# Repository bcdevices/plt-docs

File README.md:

# plt-docs

Reference material for BCD's
[Production Line Tool (PLT)](https://www.bcdevices.com/plt/)

- [GetPLT](https://plt.bcdevices.com/): PLT Support Site
- [PLT Announcements](https://plt.bcdevices.com/hc/en-us/sections/360002542332-Announcements)
- [Blue Clover Devices](https://www.bcdevices.com/)

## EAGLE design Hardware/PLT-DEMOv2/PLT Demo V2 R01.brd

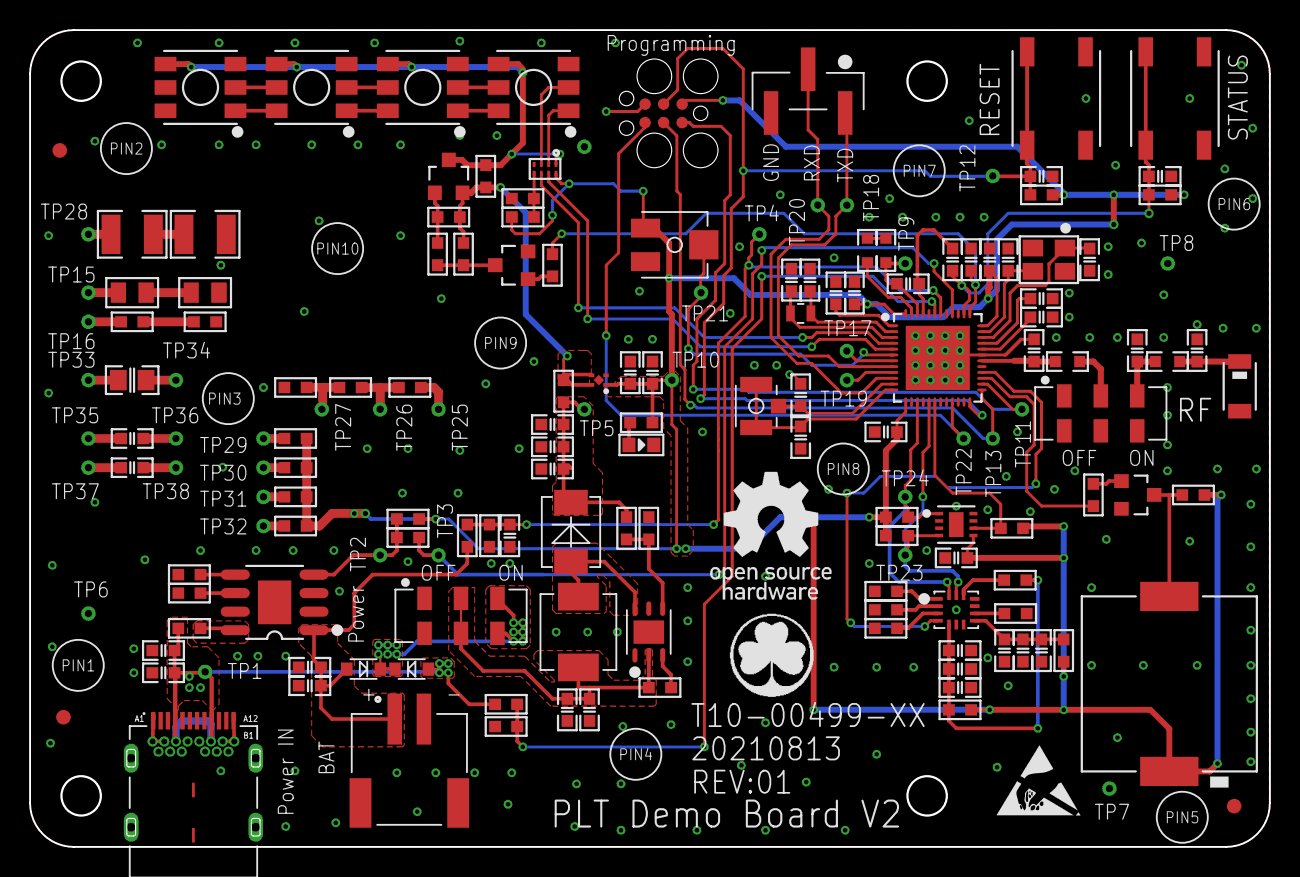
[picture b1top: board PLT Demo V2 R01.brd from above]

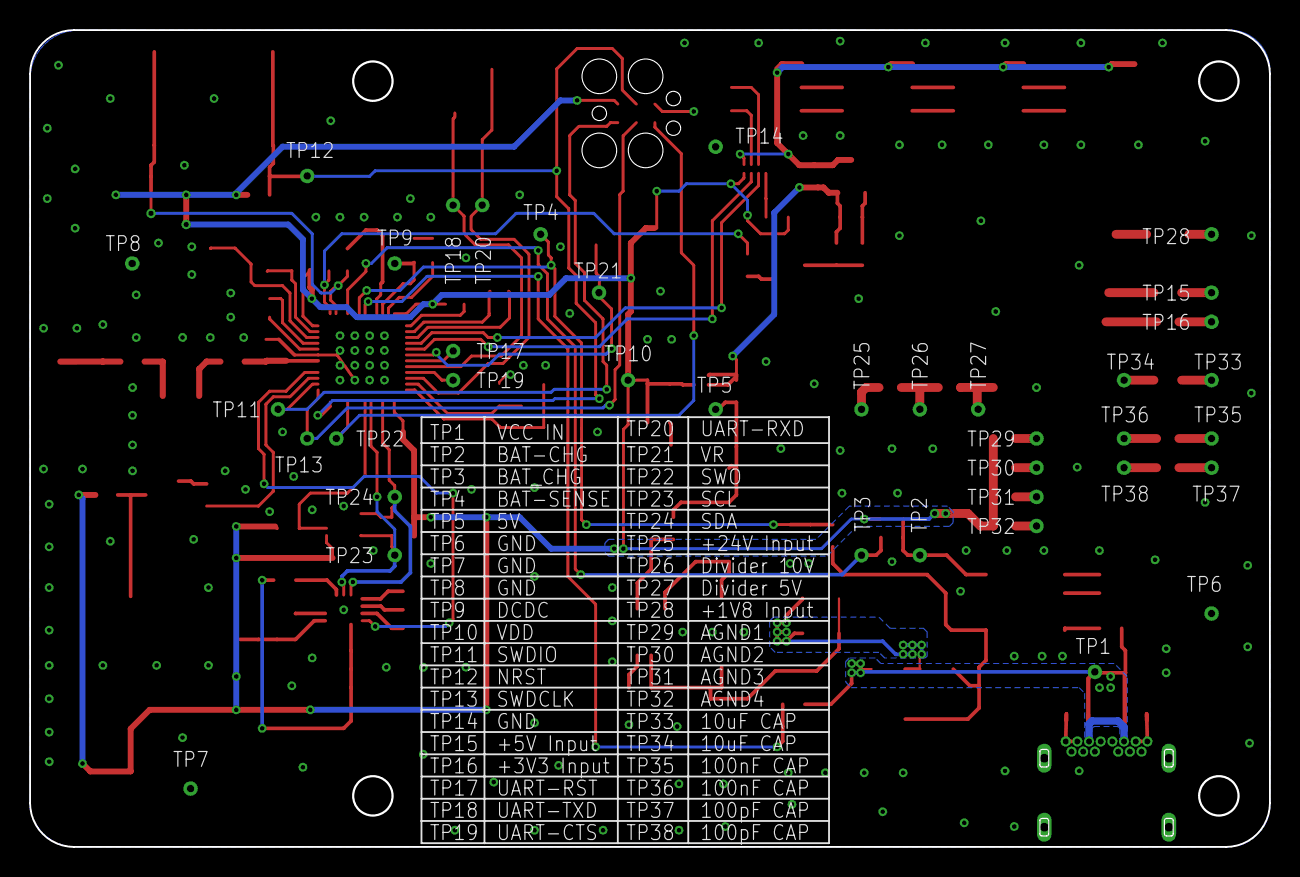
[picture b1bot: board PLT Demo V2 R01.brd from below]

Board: 2 copper layers, 85.0 x 56.0 mm, 181 parts (38 on the bottom side), 94 nets.

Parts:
ANT1: AMCA31-2R450G-S1F-T3; ANT_3216
C1, C3, C12: 10uF; C0603
C2, C4, C11, C13, C15, C18, C20, C27, C28, C32, C37, C43: 100nF; C0603
C5: 22nF; C0603
C6, C16, C19, C21, C23, C33: 12pF; C0603
C7, C8, C9, C10: 22uF; C0603
C14: 1uF; C0603
C17: 4.7uF; C0603
C22, C44: 100pF; C0603
C24, C26, C34: NC; C0603
C25: 0.8pF; C0603
C29, C30: 68pF; C0603
C31, C38: 2.2uF; C0603
C35, C36: 10nF; C0603
C39: 0.1uF; C0603
C42: 10uF; C0805
D1: B340LB-13-F; SMB
D4, D5, D6, D7: APA102C; LED5X5-6N
D8: Green; LED0603
D9, D10: CUS10S30,H3F; SOD-323
FID1, FID2, FID3: SENSOR_MISC_FIDUCIAL-1MM
J1: 632723300011; 632723X00011
J2: S2B-PH-SM4-TB(LF)(SN)
J3: U.FL-R-SMT(10)
JP1: TSM-103-01-F-SV-P-TR; JMP254P1X3V-SMT
L1: IHLP2020BZER5R6M01; IND-5220_SMD
L3: 15nH; IND-0603
L4: 10uH; IND-0603
L5: 3.9nH; IND-0603
L6: 12pF; IND-0603
P1: TC2030-MCP-NL; TC2030-IDC
PIN1, PIN2, PIN3, PIN4, PIN5, PIN6, PIN7, PIN8, PIN9, PIN10: PRESS-PINS
Q1, Q2: MMBT3904-TP; SOT23
Q3: FDN340P; SOT23
R1: 10M; R0603
R2: 2.2M; R0603
R3, R9, R12, R24, R33, R49, R50: 10K; R0603
R4, R7: 470R; R0603
R5, R34, R35, R57, R58, R59, R60: 4.7K; R0603
R6, R13, R15, R16, R18, R21, R25, R43: 0R; R0603
R8: 30K; R0603
R10, R30: 100K; R0603
R11, R14, R17, R23, R28: 47K; R0603
R20, R32, R46, R47: NC; R0603
R22: 43K; R0603
R29, R31: 470K; R0603
R48: 28K; R0603
R51, R54: 0.82R; R1210
R52, R55: 15R; R0805
R53, R56: 243K; R0603
SP1: PKLCS1212E4001R1; SPEAKER12X12_SMT
SW1, SW2: EVQ-Q2F01W; SWITCH6.5X6_SMD
SW3, SW4: JS202011JCQN
TP1, TP2, TP3, TP4, TP5, TP6, TP7, TP8, TP9, TP10, TP11, TP12, TP13, TP14, TP15, TP16, TP17, TP18, TP19, TP20, TP21, TP22, TP23, TP24, TP25, TP26, TP27, TP28, TP29, TP30, TP31, TP32, TP33, TP34, TP35, TP36, TP37, TP38: TPTP1.0X0.5_DIP; TP1.0X0.5_DIP
U1: XC6804A3E1QR-G; SOP127P6X1.6-8NP
U2: LMR62421XSDE/NOPB; WSON095P3X3-6NPAD
U3: NCP161BMX330TBG; XDFN4
U4: SHT30-DIS; DFN050P2.5X2.5-8N
U5: NRF52832-QFAA-R; QFN040P6X6-48NV
U6: BMI160; LGA050P3X2.5-14N
U7: 74LVCH2T45GT,115; XSON8-SOT833-1
U$4: BCD-LOGO
U$5: ANTI-STATIC
U$6: OSHW-LOGO-R2000
VR1: 3314J-1-103E
Y1: 7V-32.000MDDE-T; OSC3.2X2.5-4N
Y2: 9HT11-32.768KDZF-T; OSC2X1.2-2N

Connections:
5V: Q3.2, R6.1, R29.2, R31.1, R32.2, U3.3, U3.4
5V_LED: D4.4, D5.4, D6.4, D7.4, Q3.3, R32.1, U7.1
+1V8OUT: R51.2, TP28.1
+3V3OUT: R53.2, TP16.1
+5VOUT: R52.2, TP15.1
+24V: R48.2, TP25.1
AGND1: R57.1, TP29.1
AGND2: R58.1, TP30.1
AGND3: R59.1, TP31.1
AGND4: R60.1, TP32.1
BAT: C3.1, C4.1, D9.1, J2.1, R1.2, U1.1
BAT_CHGB: R25.1, TP3.1, U5.40
BAT_CHGB2: R24.1, R25.2, TP2.1, U1.4
BAT_SENSE: C5.1, R1.1, R2.2, TP4.1, U5.42
BUTTON1: C6.1, C15.1, R11.1, SW1.1, SW1.2, U5.38
BUZZER: R5.1, U5.27
DCDC: C14.1, L3.1, TP9.1, U5.46
GND: C1.2, C2.2, C3.2, C4.2, C5.2, C6.2, C7.2, C8.2, C9.2, C10.2, C11.2, C12.2, C13.2, C14.2, C15.2, C16.2, C17.2, C18.1, C19.2, C20.2, C21.1, C22.2, C23.1, C24.2, C25.2, C26.2, C27.2, C28.2, C29.2, C30.2, C31.2, C32.2, C33.2, C34.2, C35.2, C36.2, C37.2, C38.2, C39.1, D4.3, D5.3, D6.3, D7.3, D8.2, J1.A1, J1.A12, J1.B1, J1.B12, J1.GND, J1.GND1, J1.S1, J1.S2, J1.S3, J1.S4, J1.S5, J1.S6, J2.2, J2.S1, J2.S2, JP1.3, P1.5, Q1.2, Q2.2, R2.1, R3.1, R9.1, R12.1, R13.2, R17.1, R21.1, R23.1, R46.2, R47.2, R50.1, R54.1, R55.1, R56.1, SW1.3, SW1.4, SW2.3, SW2.4, TP6.1, TP7.1, TP8.1, TP14.1, U1.3, U1.9, U2.1, U2.5, U2.7, U3.2, U3.5, U4.2, U4.7, U4.8, U4.9, U5.31, U5.45, U5.49, U5.P$1, U5.P$2, U5.P$3, U5.P$4, U5.P$5, U5.P$6, U5.P$7, U5.P$8, U5.P$9, U5.P$10, U5.P$11, U5.P$12, U5.P$13, U5.P$14, U5.P$15, U5.P$16, U6.6, U6.7, U7.4, VR1.1, Y1.2, Y1.4
I2C_SCL: R35.1, TP23.1, U4.4, U5.17, U6.13
I2C_SDA: R34.1, TP24.1, U4.1, U5.15, U6.14
INT1: U5.28, U6.4
unnamed: R47.1, U6.3
unnamed: D1.1, L1.2, U2.6
unnamed: C7.1, C8.1, L1.1, R10.2, SW4.2, SW4.5, U2.2
unnamed: R10.1, U2.3
unnamed: R3.2, U1.5
unnamed: R43.1, U1.8
unnamed: R8.1, R9.2, U2.4
unnamed: C9.1, C10.1, C11.1, D1.2, R6.2, R8.2, TP5.1
unnamed: C18.2, U5.1
unnamed: C21.2, U5.2, Y2.1
unnamed: D8.1, R7.1
unnamed: R12.2, U1.6
unnamed: Q2.3, R29.1, R30.2
unnamed: Q2.1, R28.1
unnamed: Q3.1, R30.1, R31.2
unnamed: C23.2, U5.3, Y2.2
unnamed: C30.1, J3.2, J3.3, U5.12
unnamed: C29.1, J3.1, U5.11
unnamed: R13.1, U6.1
unnamed: C25.1, L5.1, U5.30
unnamed: L3.2, L4.1
unnamed: L4.2, U5.47
unnamed: D4.1, U7.2
unnamed: D4.2, U7.3
unnamed: D4.6, D5.1
unnamed: D4.5, D5.2
unnamed: D5.6, D6.1
unnamed: D5.5, D6.2
unnamed: D6.6, D7.1
unnamed: D6.5, D7.2
unnamed: R17.2, U6.9
unnamed: R20.1, R21.2, U7.5
unnamed: C16.1, U5.35, Y1.3
unnamed: Q1.3, R4.1, SP1.2
unnamed: Q1.1, R5.2
unnamed: C19.1, U5.34, Y1.1
unnamed: C22.1, U5.33
unnamed: C24.1, U5.32
unnamed: L5.2, SW3.2
unnamed: C26.1, L6.1, SW3.3
unnamed: ANT1.1, C34.1, L6.2
unnamed: C31.1, C32.1, C35.1, R15.1, R16.1, U6.5
unnamed: R16.2, U6.12
unnamed: C36.1, C37.1, C38.1, R18.1, U6.8
unnamed: R51.1, R54.2
unnamed: R52.1, R55.2
unnamed: R53.1, R56.2
unnamed: R46.1, U6.2
unnamed: D9.2, D10.2, SW4.3, SW4.6
unnamed: R49.1, R50.2, TP27.1
unnamed: R48.1, R49.2, TP26.1
unnamed: C42.2, TP34.1
unnamed: C42.1, TP33.1
unnamed: C43.2, TP36.1
unnamed: C43.1, TP35.1
unnamed: C44.2, TP38.1
unnamed: C44.1, TP37.1
NRST: C28.1, P1.3, R14.2, SW2.1, SW2.2, TP12.1, U5.24
PWR_EN: C33.1, R28.2, U5.37
RGBLED_MOSI: U5.5, U7.7
RGBLED_SCK: U5.4, U7.6
SHT30_RESET: R33.1, U4.6, U5.18
SWDCLK: P1.4, TP13.1, U5.25
SWDIO: P1.2, TP11.1, U5.26
SWO: P1.6, TP22.1, U5.21
UART_CTS: TP19.1, U5.9
UART_RTS: TP17.1, U5.7
UART_RXD: JP1.2, TP20.1, U5.10
UART_TXD: JP1.1, TP18.1, U5.8
USB_DETECT: R22.1, R23.2, U5.43
VBUS: C1.1, C2.1, D10.1, J1.A4, J1.A9, J1.B4, J1.B9, R22.2, R43.2, TP1.1
VDD: C12.1, C13.1, C17.1, C20.1, C27.1, C39.2, P1.1, R4.2, R7.2, R11.2, R14.1, R15.2, R18.2, R20.2, R24.2, R33.2, R34.2, R35.2, R57.2, R58.2, R59.2, R60.2, SP1.1, TP10.1, U3.1, U4.5, U5.13, U5.36, U5.48, U7.8, VR1.3
VR: TP21.1, U5.6, VR1.2

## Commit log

2018-12-04 suite-demo1-BLE: nRF52DK test plan
2018-12-31 Add STM32L4DK-IOT example
2019-01-04 Add suite-scan.yaml
2019-01-11 Add ly10 demo FW v0.1.0
2019-01-11 Add ly10 demo FW v0.1.0 (#1)
2019-01-17 Add LY10-DEMO firmware v0.1.4, v0.1.5, v0.1.6
2019-01-17 Add LY10-DEMO firmware v0.1.4, v0.1.5, v0.1.6 (#2)
2019-01-17 Update README.md (#3)
2019-01-21 LY10-DEMO: v0.1.7, v0.1.8
2019-01-21 LY10-DEMO: v0.1.7, v0.1.8 (#4)
2019-03-08 Add Test Suite Reference v0.4.7
2019-03-08 Add Test Suite Reference v0.4.7 (#5)
2019-03-09 Update to Test Plan Reference v0.4.8 (#6)
2019-03-09 rename
2019-03-28 Update TestPlanReference to v0.4.9 (#7)
2019-03-31 Update TestPlanReference to v0.5.0
    - Document `freq` command
    - Document `measure` command
    - Document `mux` command
    - Document `pin` command
    - Document `power` command
    - Document `short` command
2019-03-31 Update TestPlanReference to v0.5.0 (#8)
    - Document `freq` command
    - Document `measure` command
    - Document `mux` command
    - Document `pin` command
    - Document `power` command
    - Document `short` command
2019-04-09 Document ESP32 DevKitC hookup
2019-04-09 README: update link
2019-04-09 Document ESP32 DevKitC hookup (#9)
    * Document ESP32 DevKitC hookup
    * README: update link
2019-04-10 PLT-200A: rear DUT connectors
2019-04-10 PLT-200A: rear DUT connectors (#10)
2019-04-10 PLT-200A probes and signals
2019-04-10 PLT-200A probes and signals (#11)
2019-04-11 Add PLT-200A test probe assignments Excel template
2019-04-15 Document programming CC1352
2019-04-15 Document programming CC1352 (#12)
2019-04-16 Add TestPlanReference v0.5.1
2019-04-18 LY10-DEMO: update for PLT-200A
2019-04-19 Add drawings for PLT-200A rear IDC receptacles
2019-05-13 Add LY10-DEMO ICT test plan v1.2
2019-05-14 Add TestPlanReference v0.5.2
2019-05-14 Add NFC write example
2019-07-02 update README (#13)
2019-07-02 Add PLT-200A Specificaition Sheet v0.5.1
2019-07-02 Add PLT-200A Specificaition Sheet v0.5.1 (#15)
2019-07-18 nRF52DK: Add example firmware
2019-07-18 nRF52DK: Add HRS firmware (#16)
    * nRF52DK: Add example firmware
2019-07-22 ICTDemoTestPlanV1.3.yaml
    Update of ICTDemoTestPlanV1.2.yaml, where the impedance range for ICT-005 was changed to >-1Ohm.
2019-07-24 Add Zephyr-based LY10 demo firmware
2019-07-24 Add Zephyr-based LY10 demo firmware (#18)
2019-07-24 Rename
    * Rename
2019-08-15 ICTZephyrTestPlanV1.3: Fix firmware HEX path
2019-08-15 ICTZephyrTestPlanV1.3: Fix firmware HEX path (#20)
2019-08-15 suite-stm32l4DK-IOT-BLE.yaml: Fix firmware path
2019-08-15 suite-stm32l4DK-IOT-BLE.yaml: Fix firmware path (#21)
2019-08-19 Add ATMega168PB example project
2019-08-19 Add ATMega168PB example project (#22)
2019-08-19 Add manual v0.5.6
2019-08-19 Dev/manual 0.5.6 (#23)
    * Add ATMega168PB example project
    * Add manual v0.5.6
2019-08-21 CC1352 Project: Update README
2019-08-21 STM32L4DK-IOT: Update README
2019-08-21 nRF52DK Project: Update README
2019-08-21 Atmel AVR ATmega168P/PB Project: update README
2019-08-21 README.md: update
2019-08-21 README.md: update (#25)
2019-08-21 Add nRF91 DK Project
2019-08-21 update README links
2019-08-21 nRF91 DK: Program via SWD
2019-08-21 Add nRF91 DK Project (#26)
    * Add nRF91 DK Project
    * update README links
    * nRF91 DK: Program via SWD
2019-08-22 Test Plan Reference v0.5.7
2019-08-26 PLT-200A Specification Sheet v0.5.8
2019-08-26 PLT-200A Specification Sheet v0.5.8 (#28)
2019-09-19 System Manual v0.6.0
2019-09-19 System Manual v0.6.0 (#29)
2019-09-19 System Manual v0.6.1
2019-09-19 System Manual v0.6.1 (#30)
2019-09-19 Remove older docs
2019-09-19 Remove older docs (#31)
2019-10-04 PLT System Documentation v0.6.2
2019-10-04 Add links to latest PDFs
2019-10-08 PLT System Documentation v0.6.3
2019-10-08 PLT System Documentation v0.6.3 (#32)
2019-10-08 PLTcloud spec sheet
2019-10-08 PLTcloud spec sheet (#33)
2019-11-05 ICT spec sheet
2019-11-05 ICT spec sheet (#34)
2019-11-07 Add TestPlanReference-0.6.5.pdf
2019-12-30 Duplicate Test probe assignments TEMPLATE under new name
2020-02-20 v0.6.7 spec sheets
2020-02-20 STM32L4DK-IOT: Use STM32L4_IoT_STLink target name
2020-02-20 suite-hrs-BLE: Use nRF52_JLink target name
2020-02-20 at_client-JLink: Use nRF91_JLink target name
2020-02-20 Add STM32F4DISCOVERY example project
2020-02-20 Add STM32F4DISCOVERY example project (#35)
2020-02-21 Test Plans for AT-based GSM modems
2020-02-21 Test Plans for AT-based GSM modems (#36)
2020-02-22 Test Plans for Nucleo F401RE board
2020-02-22 Test Plans for Nucleo F401RE board (#37)
2020-02-22 Test Plans for Nucleo L432KC board
2020-02-24 Zephyr sample for STM32Nucleo-F207ZG
2020-02-24 Zephyr sample for nRF52DK
2020-02-24 Zephyr sample for nRF91DK
2020-02-24 Zephyr sample for nRF52DK (#39)
2020-02-24 Zephyr sample for nRF91DK (#40)
2020-02-24 Update HEX files
2020-02-24 Zephyr sample for STM32Nucleo-F207ZG (#38)
    * Zephyr sample for STM32Nucleo-F207ZG
2020-02-24 Add TestPlanReference 0.6.8
2020-02-24 Zephyr sample for NXP LPCXpresso 11C24
2020-02-24 Add zephyr nRF91 example project (#41)
    * Zephyr sample for nRF91DK
    * Add TestPlanReference 0.6.8
2020-02-24 Zephyr sample for NXP LPCXpresso 11C24 (#42)
2020-02-24 README.md: Fix title
2020-02-24 STM32F4 Discovery Zephyr CAN sample
2020-02-24 STM32F4 Discovery Zephyr CAN sample (#43)
2020-02-26 README.md: Add LPCXpresso 11C24, Nucleo F207ZG
2020-03-06 Add PNEV7462C example Project
2020-03-06 Add PNEV7462C example Project (#44)
2020-03-09 TPM: Add GND
2020-03-09 TPM: Add GND (#45)
    Update test point matrix to include GND
2020-03-09 Examples: remove 'none' from program commands
2020-03-09 Examples: remove 'none' from program commands (#46)
2020-03-31 Add PSoC6 example
2020-04-22 LPCXpresso11C24: Add CMSIS-DAP example
2020-05-01 Add PSoC4 example
2020-07-17 Add EFM32-STK3800 example
2020-08-13 Add Microchip Explorer 8 / PIC18F25K20 example
2020-12-22 Add ATSAME54-XPro Zephyr sample project
2021-04-27 Move targets
2021-04-27 Targets to Boards
2021-04-27 PLT-DEMO
2021-04-28 PLT-DEMO: Rename artefacts to PLT-DEMO-..
2021-04-28 Projects: update README
2021-08-23 ATSAME54-XPro: README
2021-08-23 ATSAME54-XPro: README images
2021-08-23 ATSAME54-XPro: README cable pitch
2021-08-31 ATSAME54-XPro: 5 second delay after erase
2021-09-28 Add PLT-DEMOv2 schematics
2021-09-28 move
2021-09-28 Add CERN Open Hardware Licence Version 2 - Strongly Reciprocal
2021-12-17 Add Zephyr blinky example for TI CC1352r1_launchxl, update example test plan.
2021-12-20 Add ESP32 Zephyr hello_world sample.
2021-12-21 Add ESP32 Zephyr hello_world sample. (#48)
2022-10-28 Add nucleo-h753 examples.
2022-10-28 Fix directory name.
2022-10-28 Fix file names.
2022-10-31 Add example projects for NUCLEO-F070RB and NUCLEO-L152RE.
2022-11-02 Adjust STM32L1 programming target to STM32L1_Cat456.
    There are 6 categories of STM32L1, with different memory structures.
2022-11-02 Add example projects for NUCLEO-F070RB and NUCLEO-L152RE. (#50)
    * Add example projects for NUCLEO-F070RB and NUCLEO-L152RE.
    * Adjust STM32L1 programming target to STM32L1_Cat456.
    There are 6 categories of STM32L1, with different memory structures.
2022-11-02 Add example project for NUCLEO-H753ZI (#49)
    * Add nucleo-h753 examples.
    * Fix directory name.
    * Fix file names.
2022-11-07 Add example project for Raspberry Pi Pico, using USB Mass Storage
2022-11-09 Add example project for Raspberry Pi Pico, using USB Mass Storage (#51)
2023-01-26 Add example project for Analog Devices MAX32690EVKit
2023-01-26 Add example project for Analog Devices MAX32690EVKit (#52)
2023-02-16 Add example project for ST NUCLEO-G474RE.
2023-02-20 Add example project for ST NUCLEO-G474RE. (#53)
2023-03-20 cleanups
2023-03-20 link fixes
2023-03-20 cleanup
2023-03-20 Update pltdemov2 README.md (#54)
2023-03-29 yamllint
2023-03-29 yamllint (#55)
2023-04-19 ATSAMG55-XPro Sample Project
2023-04-20 ATSAMG55-XPro Sample Project (#56)
2023-05-19 Zephyr sample firmware binaries
    (Imported from plt-docs-zephyr-fw v0.1.1, built from zephyr v3.3.0)
    - Microchip:
    atsamd20_xpro, atsamd21_xpro, atsame54_xpro, sam4e_xpro,
    sam4l_ek, sam4s_xplained, sam_e70_xplained, sam_v71_xult
    - Nordic:
    blueclover_plt_demo_v2_nrf52832, nrf52840dk_nrf52840,
2023-05-19 Zephyr sample firmware binaries (#57)
    (Imported from plt-docs-zephyr-fw v0.1.1, built from zephyr v3.3.0)
    - Microchip:
    atsamd20_xpro, atsamd21_xpro, atsame54_xpro, sam4e_xpro,
    sam4l_ek, sam4s_xplained, sam_e70_xplained, sam_v71_xult
    - Nordic:
    blueclover_plt_demo_v2_nrf52832, nrf52840dk_nrf52840,
2023-05-25 zephyr-samples: SiFive
2023-05-25 zephyr-samples: SiFive (#58)
2023-05-30 zephyr-samples: Espressif, RPi, NXP i.MX93, nRF51
    Zephyr sample binaries for additional target platforms.
2023-05-30 zephyr-samples: Espressif, RPi, NXP i.MX93, nRF51 (#59)
    Zephyr sample binaries for additional target platforms.
2024-01-02 Update CC1352 Programming Example for PLT-300, CMSIS-DAP
2024-01-05 Update CC1352 Programming Example for PLT-300, CMSIS-DAP (#60)
